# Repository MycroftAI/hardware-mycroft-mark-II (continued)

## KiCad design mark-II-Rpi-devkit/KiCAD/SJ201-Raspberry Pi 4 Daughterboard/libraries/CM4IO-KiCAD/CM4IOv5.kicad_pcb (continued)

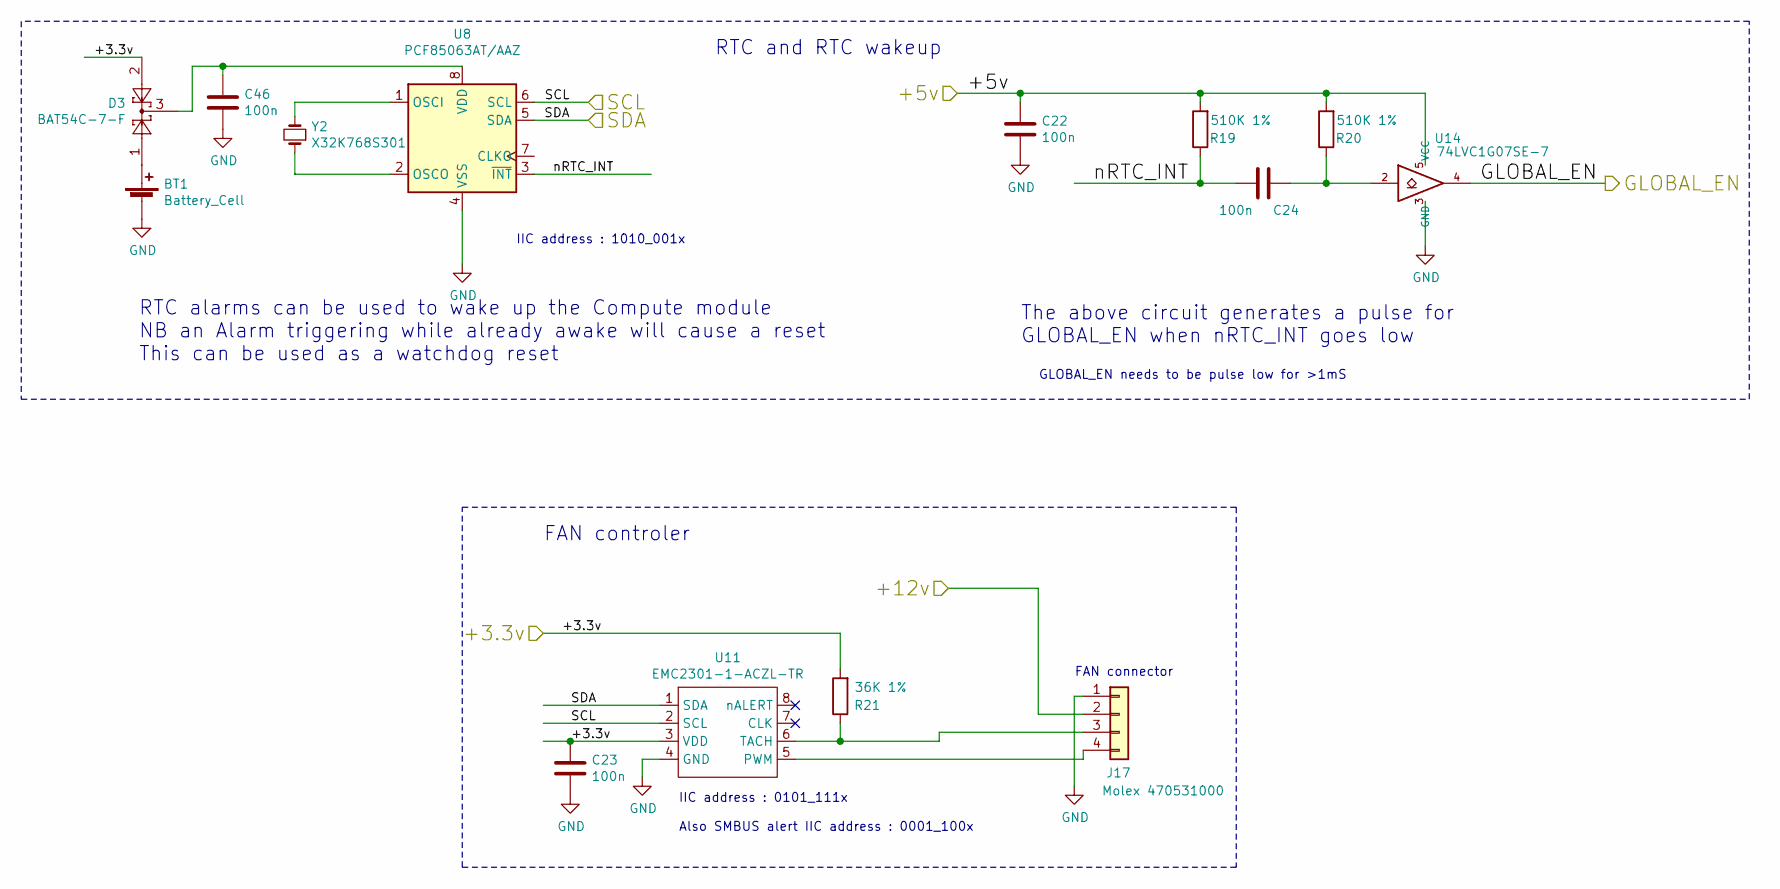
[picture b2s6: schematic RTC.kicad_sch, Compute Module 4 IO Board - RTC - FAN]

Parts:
BT1: Battery_Cell; BatteryHolder_Keystone_3034_1x20mm; Part Description Battery Retainer Coin, 20.0mm 1 Cell SM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
C22, C23, C24, C46: 100n; C_0402_1005Metric; Part Description 0.1uF 10% 16V Ceramic Capacitor X7R 040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
D3: BAT54C-7-F; SOT-23; Part Description Diode Array 1 Pair Common Cathode Schot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
J17: Molex 470531000; FanPinHeader_1x04_P2.54mm_Vertical; Part Description Connector Header Through Hole 4 positio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
R19, R20: 510K 1%; R_0402_1005Metric; Part Description Resistor 510K M1005 1% 63mW
R21: 36K 1%; R_0402_1005Metric; Part Description Resistor 36K M1005 1% 63mW
U8: PCF85063AT/AAZ; SOIC-8_3.9x4.9mm_P1.27mm; Part Description Real Time Clock (RTC) IC Clock/Calendar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
U11: EMC2301-1-ACZL-TR; SOIC-8_5.23x5.23mm_P1.27mm; Part Description Motor Driver PWM 8-MSOP
U14: 74LVC1G07SE-7; SOT-353_SC-70-5; Part Description Buffer, Non-Inverting 1 Element 1 Bit p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
Y2: X32K768S301; Crystal_SMD_3215-2Pin_3.2x1.5mm; Part Description Crystal 32.768KHz 7pF 20pmm

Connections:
/+3.3v: C23.1, D3.2, R21.2, U11.3 (VDD); also elsewhere on the board
/+5v: C22.1, R19.2, R20.2, U14.5 (VCC); also elsewhere on the board
/+12v: J17.2; also elsewhere on the board
/GLOBAL_EN: U14.4; also elsewhere on the board
/RTC , Wakeup, FAN/nRTC_INT: C24.2, R19.1, U8.3 (~INT~)
/SCL0: U8.6 (SCL), U11.2 (SCL); also elsewhere on the board
/SDA0: U8.5 (SDA), U11.1 (SDA); also elsewhere on the board
GND: BT1.2 (-), C22.2, C23.2, C46.2, J17.1, U8.4 (VSS), U11.4 (GND), U14.3 (GND); also elsewhere on the board
unnamed: BT1.1 (+), D3.1
unnamed: C24.1, R20.1, U14.2
unnamed: C46.1, D3.3, U8.8 (VDD)
unnamed: J17.3, R21.1, U11.6 (TACH)
unnamed: J17.4, U11.5 (PWM)
unnamed: U8.1 (OSCI), Y2.2
unnamed: U8.2 (OSCO), Y2.1

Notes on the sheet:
RTC alarms can be used to wake up the Compute module NB an Alarm triggering while already awake will cause a reset This can be used as a watchdog reset
IIC address : 1010_001x
FAN controler
IIC address : 0101_111x
Also SMBUS alert IIC address : 0001_100x
RTC and RTC wakeup
The above circuit generates a pulse for GLOBAL_EN when nRTC_INT goes low
GLOBAL_EN needs to be pulse low for >1mS
FAN connector

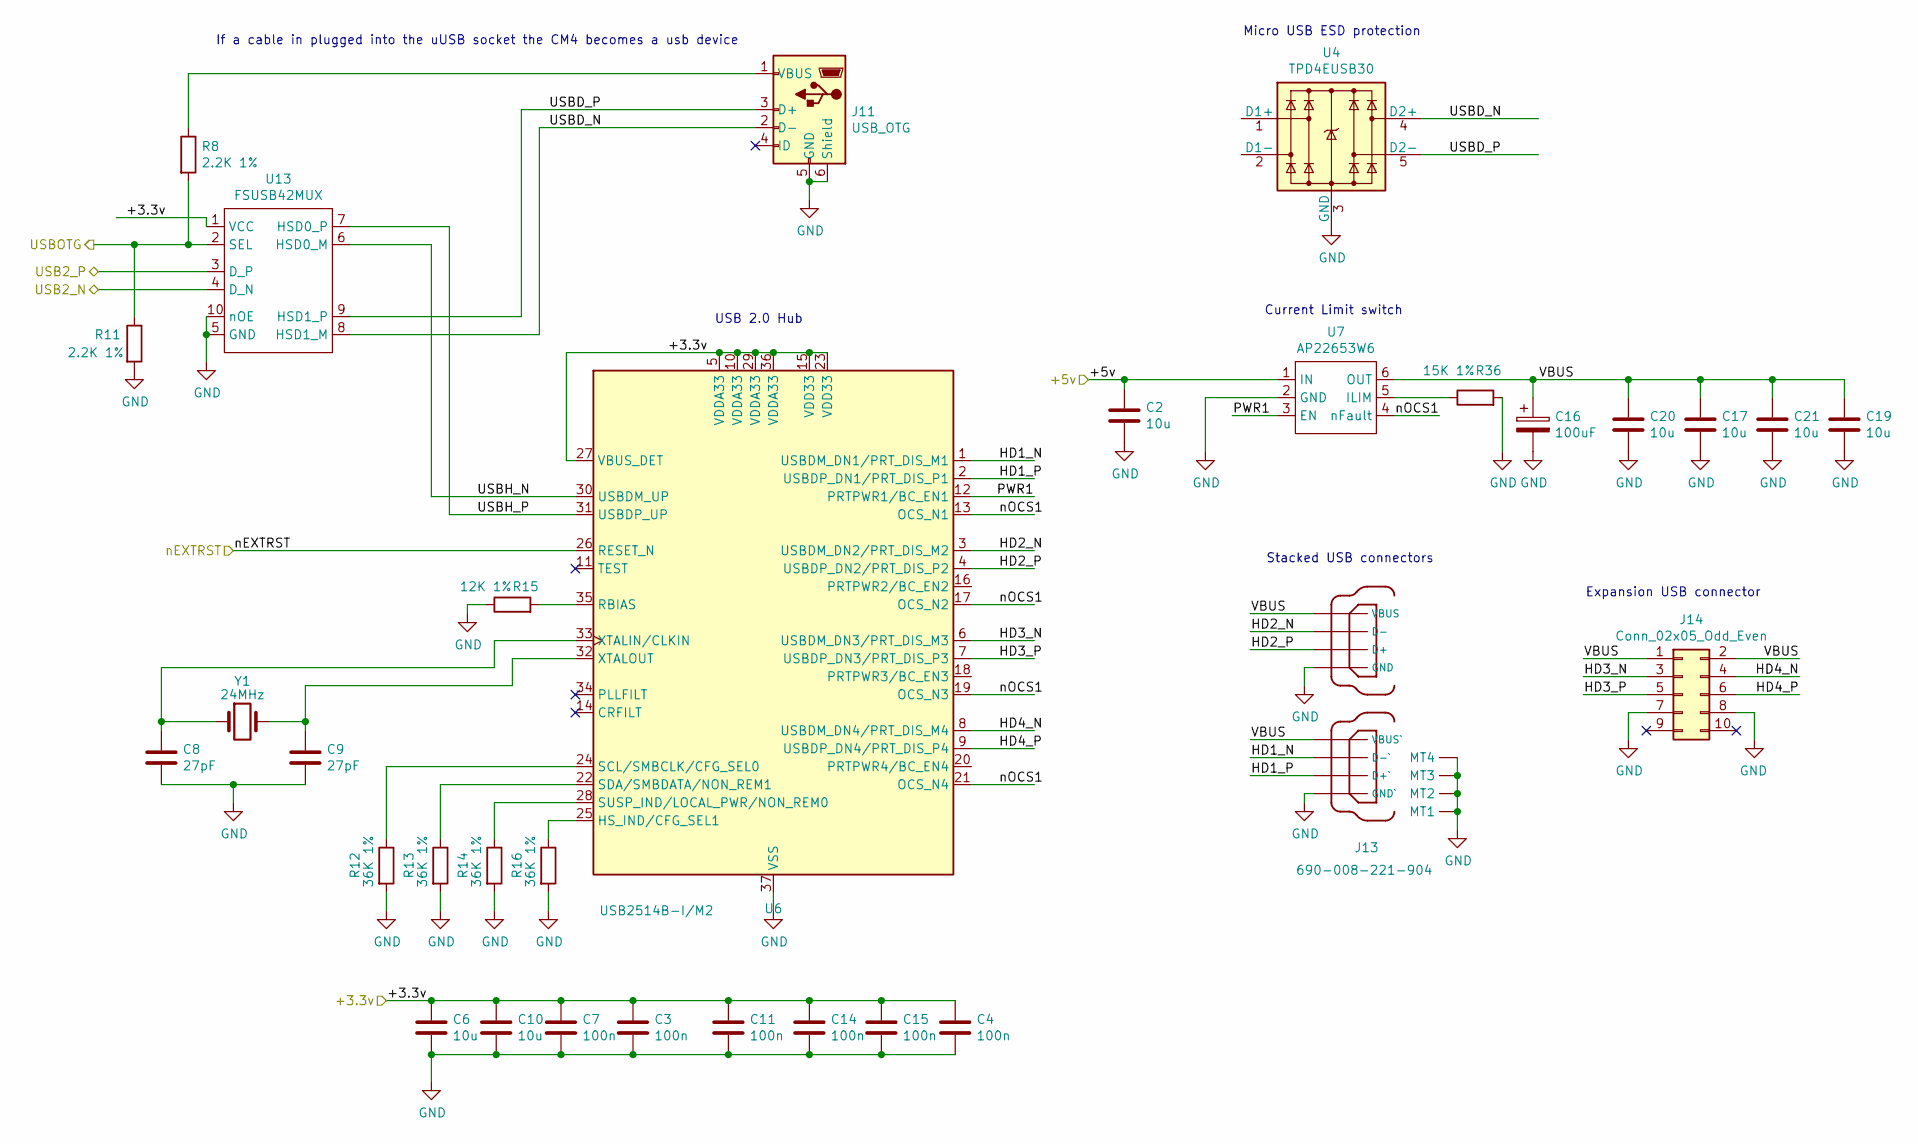
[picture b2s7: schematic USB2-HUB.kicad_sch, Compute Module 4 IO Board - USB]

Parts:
C2, C6, C10, C17, C19, C20, C21: 10u; C_0805_2012Metric; Part Description 10uF 10% 10V Ceramic Capacitor X7R 0805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
C3, C4, C7, C11, C14, C15: 100n; C_0402_1005Metric; Part Description 0.1uF 10% 16V Ceramic Capacitor X7R 040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
C8, C9: 27pF; C_0402_1005Metric; Part Description 27pF 5% 50V Ceramic Capacitor C0G, NP0 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
C16: 100uF; CP_EIA-7343-31_Kemet-D; Part Description Capacitor, SP-Cap, 100u, 6.3V, 15mR ESR
J11: USB_OTG; USB_Micro-B_EDAC_UCON00686; Part Description USB - micro B USB 2.0 Receptacle Connec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
J13: 690-008-221-904; MOLEX_USB_67298-4090; Part Description USB-A (USB TYPE-A), Stacked Receptacle 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
J14: Conn_02x05_Odd_Even; PinHeader_2x05_P2.54mm_Vertical; Part Description PinHeader_2x05_P2.54mm_Vertical
R8, R11: 2.2K 1%; R_0402_1005Metric; Part Description Resistor 2.2K M1005 1% 63mW
R12, R13, R14, R16: 36K 1%; R_0402_1005Metric; Part Description Resistor 36K M1005 1% 63mW
R15: 12K 1%; R_0402_1005Metric; Part Description Resistor 12K M1005 1% 63mW
R36: 15K 1%; R_0402_1005Metric; Part Description Resistor 15K M1005 1% 63mW
U4: TPD4EUSB30; USON-10_2.5x1.0mm_P0.5mm; Part Description Quad TVS diode for high speed signals (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
U6: USB2514B-I/M2; QFN-36-1EP_6x6mm_P0.5mm_EP3.7x3.7mm; Part Description USB Hub Controller USB Interface 36-SQF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
U7: AP22653W6; SOT-23-6; Part Description Power Switch/Driver 1:1 P-Channel 2.1A 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
U13: FSUSB42MUX; MSOP-10_3x3mm_P0.5mm; Part Description USB Switch IC 1 Channel 10-MSOP
Y1: 24MHz; Crystal_SMD_HC49-SD; Part Description 24MHz Crystal 18pf 30ppm 30ppm

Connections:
/+3.3v: C3.1, C4.1, C6.1, C7.1, C10.1, C11.1, C14.1, C15.1, U6.5 (VDDA33), U6.10 (VDDA33), U6.15 (VDD33), U6.23 (VDD33), U6.27 (VBUS_DET), U6.29 (VDDA33), U6.36 (VDDA33), U13.1 (VCC); also elsewhere on the board
/+5v: C2.1, U7.1 (IN); also elsewhere on the board
/USB2-HUB/HD1_N: J13.2 (D-`), U6.1 (USBDM_DN1/PRT_DIS_M1)
/USB2-HUB/HD1_P: J13.3 (D+`), U6.2 (USBDP_DN1/PRT_DIS_P1)
/USB2-HUB/HD2_N: J13.6 (D-), U6.3 (USBDM_DN2/PRT_DIS_M2)
/USB2-HUB/HD2_P: J13.7 (D+), U6.4 (USBDP_DN2/PRT_DIS_P2)
/USB2-HUB/HD3_N: J14.3, U6.6 (USBDM_DN3/PRT_DIS_M3)
/USB2-HUB/HD3_P: J14.5, U6.7 (USBDP_DN3/PRT_DIS_P3)
/USB2-HUB/HD4_N: J14.4, U6.8 (USBDM_DN4/PRT_DIS_M4)
/USB2-HUB/HD4_P: J14.6, U6.9 (USBDP_DN4/PRT_DIS_P4)
/USB2-HUB/PWR1: U6.12 (PRTPWR1/BC_EN1), U7.3 (EN)
/USB2-HUB/USBD_N: J11.2 (D-), U4.4 (D2+), U4.7, U13.8 (HSD1_M)
/USB2-HUB/USBD_P: J11.3 (D+), U4.5 (D2-), U4.6, U13.9 (HSD1_P)
/USB2-HUB/USBH_N: U6.30 (USBDM_UP), U13.6 (HSD0_M)
/USB2-HUB/USBH_P: U6.31 (USBDP_UP), U13.7 (HSD0_P)
/USB2-HUB/VBUS: C16.1, C17.1, C19.1, C20.1, C21.1, J13.1 (VBUS`), J13.5 (VBUS), J14.1, J14.2, U7.6 (OUT)
/USB2-HUB/nOCS1: U6.13 (OCS_N1), U6.17 (OCS_N2), U6.19 (OCS_N3), U6.21 (OCS_N4), U7.4 (nFault)
/USB2_N: U13.4 (D_N); also elsewhere on the board
/USB2_P: U13.3 (D_P); also elsewhere on the board
/USBOTG: R8.2, R11.1, U13.2 (SEL); also elsewhere on the board
/nEXTRST: U6.26 (RESET_N); also elsewhere on the board
GND: C2.2, C3.2, C4.2, C6.2, C7.2, C8.2, C9.2, C10.2, C11.2, C14.2, C15.2, C16.2, C17.2, C19.2, C20.2, C21.2, J11.5 (GND), J11.6 (Shield), J13.4 (GND`), J13.8 (GND), J13.MT1, J13.MT2, J13.MT3, J13.MT4, J14.7, J14.8, R11.2, R12.2, R13.2, R14.2, R15.1, R16.2, R36.2, U4.3 (GND), U4.8 (GND), U6.37 (VSS), U7.2 (GND), U13.5 (GND), U13.10 (nOE); also elsewhere on the board
unnamed: C8.1, U6.33 (XTALIN/CLKIN), Y1.1
unnamed: C9.1, U6.32 (XTALOUT), Y1.2
unnamed: J11.1 (VBUS), R8.1
unnamed: R12.1, U6.24 (SCL/SMBCLK/CFG_SEL0)
unnamed: R13.1, U6.22 (SDA/SMBDATA/NON_REM1)
unnamed: R14.1, U6.28 (SUSP_IND/LOCAL_PWR/NON_REM0)
unnamed: R15.2, U6.35 (RBIAS)
unnamed: R16.1, U6.25 (HS_IND/CFG_SEL1)
unnamed: R36.1, U7.5 (ILIM)
unnamed: U4.1 (D1+), U4.10
unnamed: U4.2 (D1-), U4.9

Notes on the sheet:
If a cable in plugged into the uUSB socket the CM4 becomes a usb device
USB 2.0 Hub
Current Limit switch
Micro USB ESD protection
Stacked USB connectors
Expansion USB connector

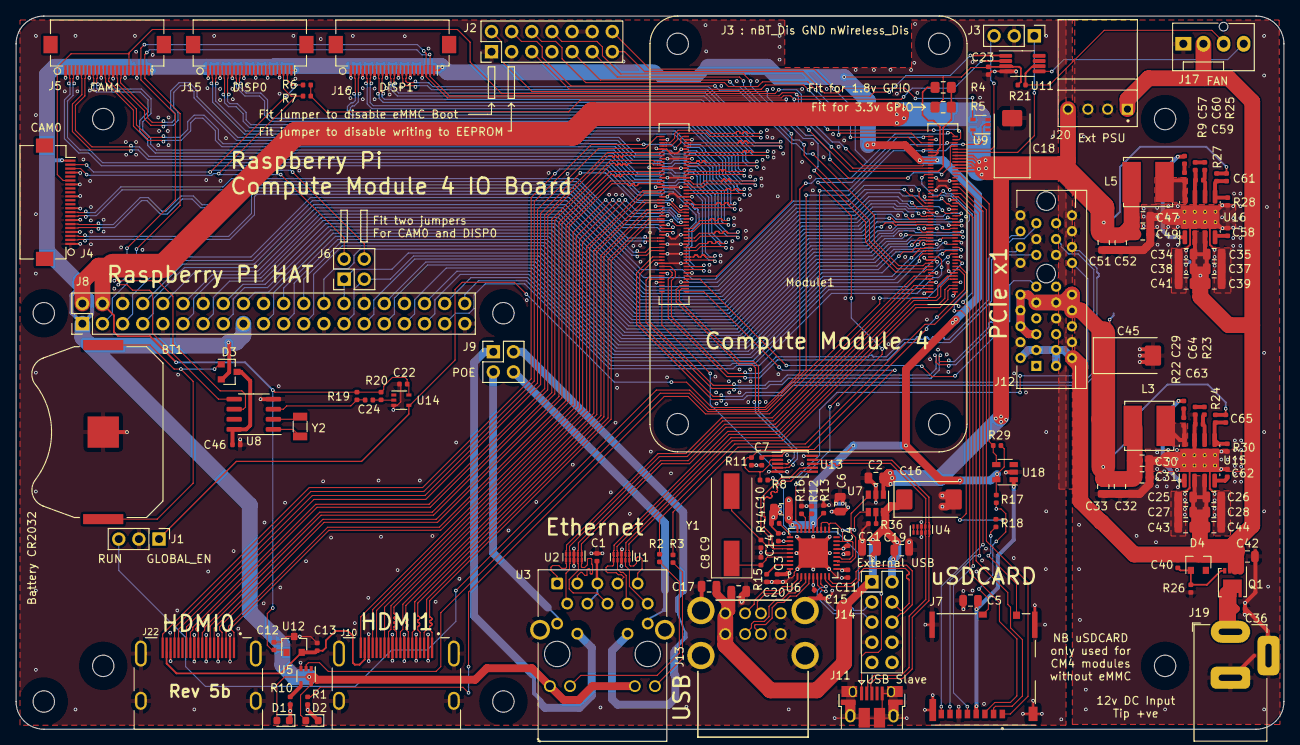
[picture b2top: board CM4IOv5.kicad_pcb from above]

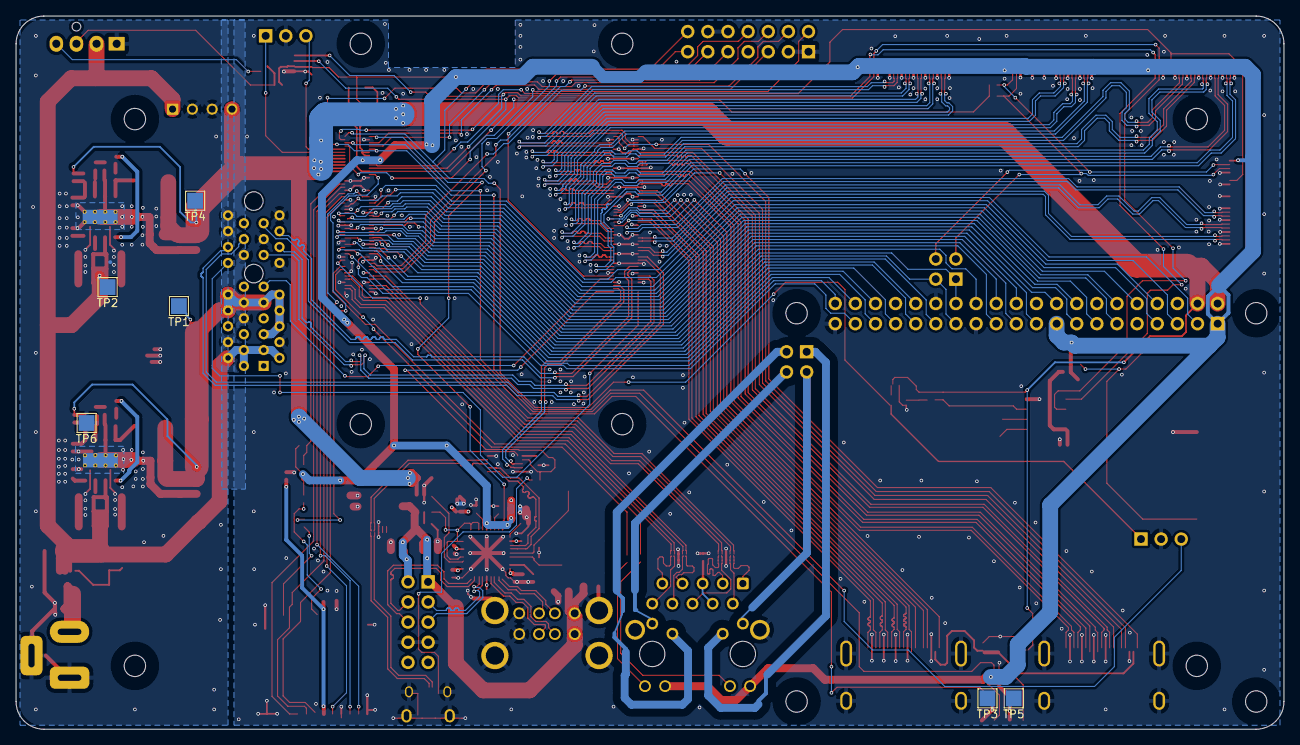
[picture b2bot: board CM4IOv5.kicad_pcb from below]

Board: 4 copper layers, 160.0 x 90.0 mm, 151 parts (6 on the bottom side), 204 nets.

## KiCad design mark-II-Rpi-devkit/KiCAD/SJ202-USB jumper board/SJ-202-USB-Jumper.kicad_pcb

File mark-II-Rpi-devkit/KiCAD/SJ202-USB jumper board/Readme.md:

**SJ202-USB Jumper Board**

*⛵️ Note that this repository is a work-in-progress. It will be updated and improved on over time.*

This board connects the Raspberry Pi 4 to the SJ201-Raspberry Pi 4 Daughterboard

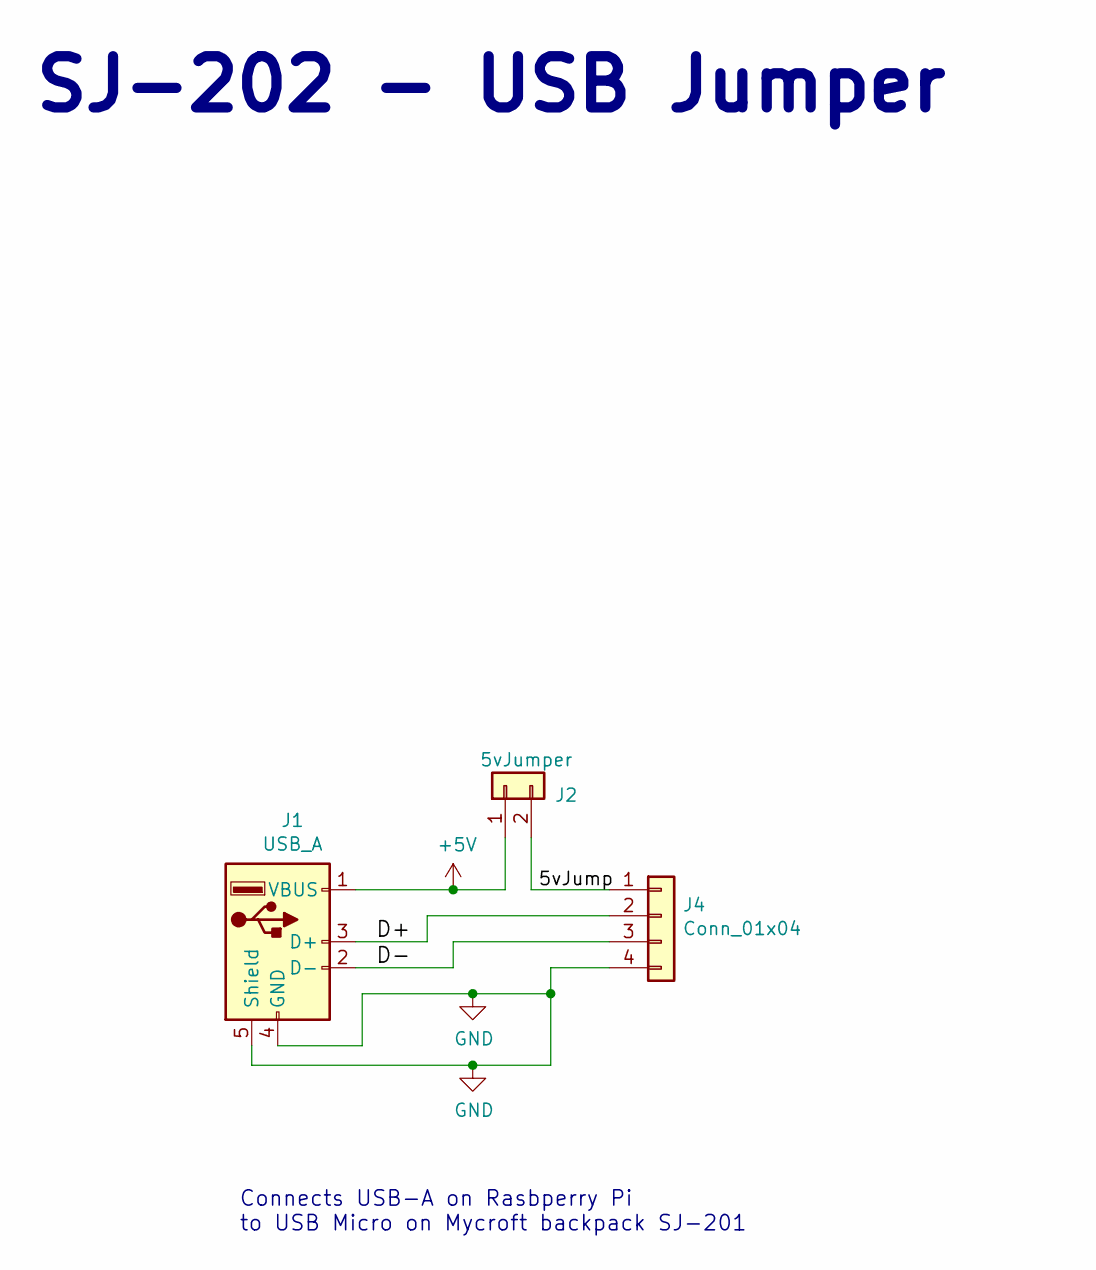
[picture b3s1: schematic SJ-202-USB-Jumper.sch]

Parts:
J1: USB_A; USB_A_Female_UE27AC54100; MPN U-G-04WS-W-03; Digikey WM3983CT-ND
J2: 5vJumper; SolderJumper-2_P1.3mm_Open_TrianglePad1.0x1.5mm; MPN DNP
J4: Conn_01x04; PinHeader_1x04_P2.54mm_Vertical; MPN 210-91-04GB01; LCSC C390680

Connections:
+5V: J1.1 (VBUS), J2.1
/5vJump: J2.2, J4.1
/D+: J1.3 (D+), J4.2
/D-: J1.2 (D-), J4.3
GND: J1.4 (GND), J1.5 (Shield), J4.4

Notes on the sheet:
SJ-202 - USB Jumper
Connects USB-A on Rasbperry Pi to USB Micro on Mycroft backpack SJ-201

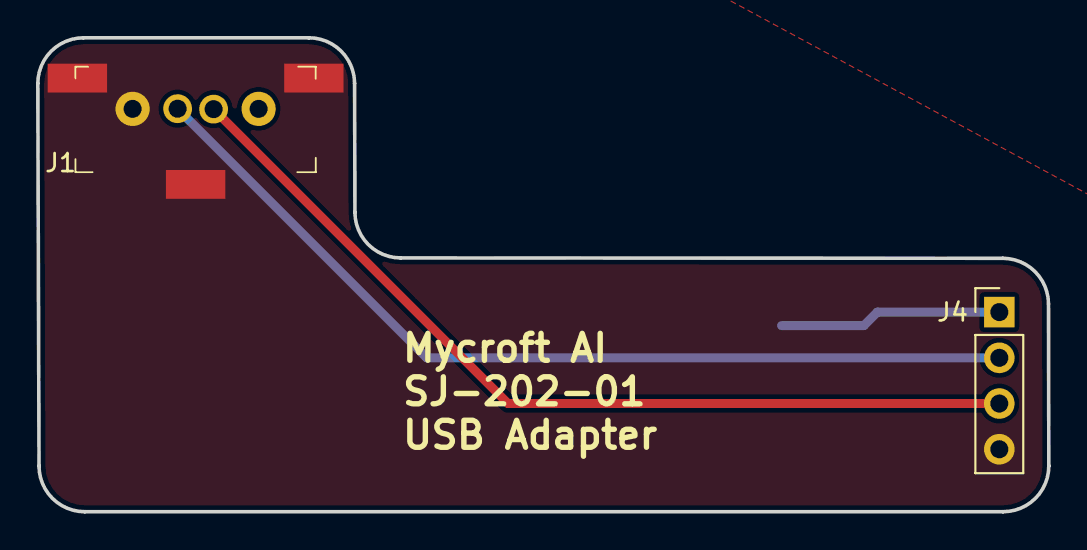
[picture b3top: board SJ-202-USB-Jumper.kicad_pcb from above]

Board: 2 copper layers, 56.2 x 26.3 mm, 3 parts (1 on the bottom side), 5 nets.
